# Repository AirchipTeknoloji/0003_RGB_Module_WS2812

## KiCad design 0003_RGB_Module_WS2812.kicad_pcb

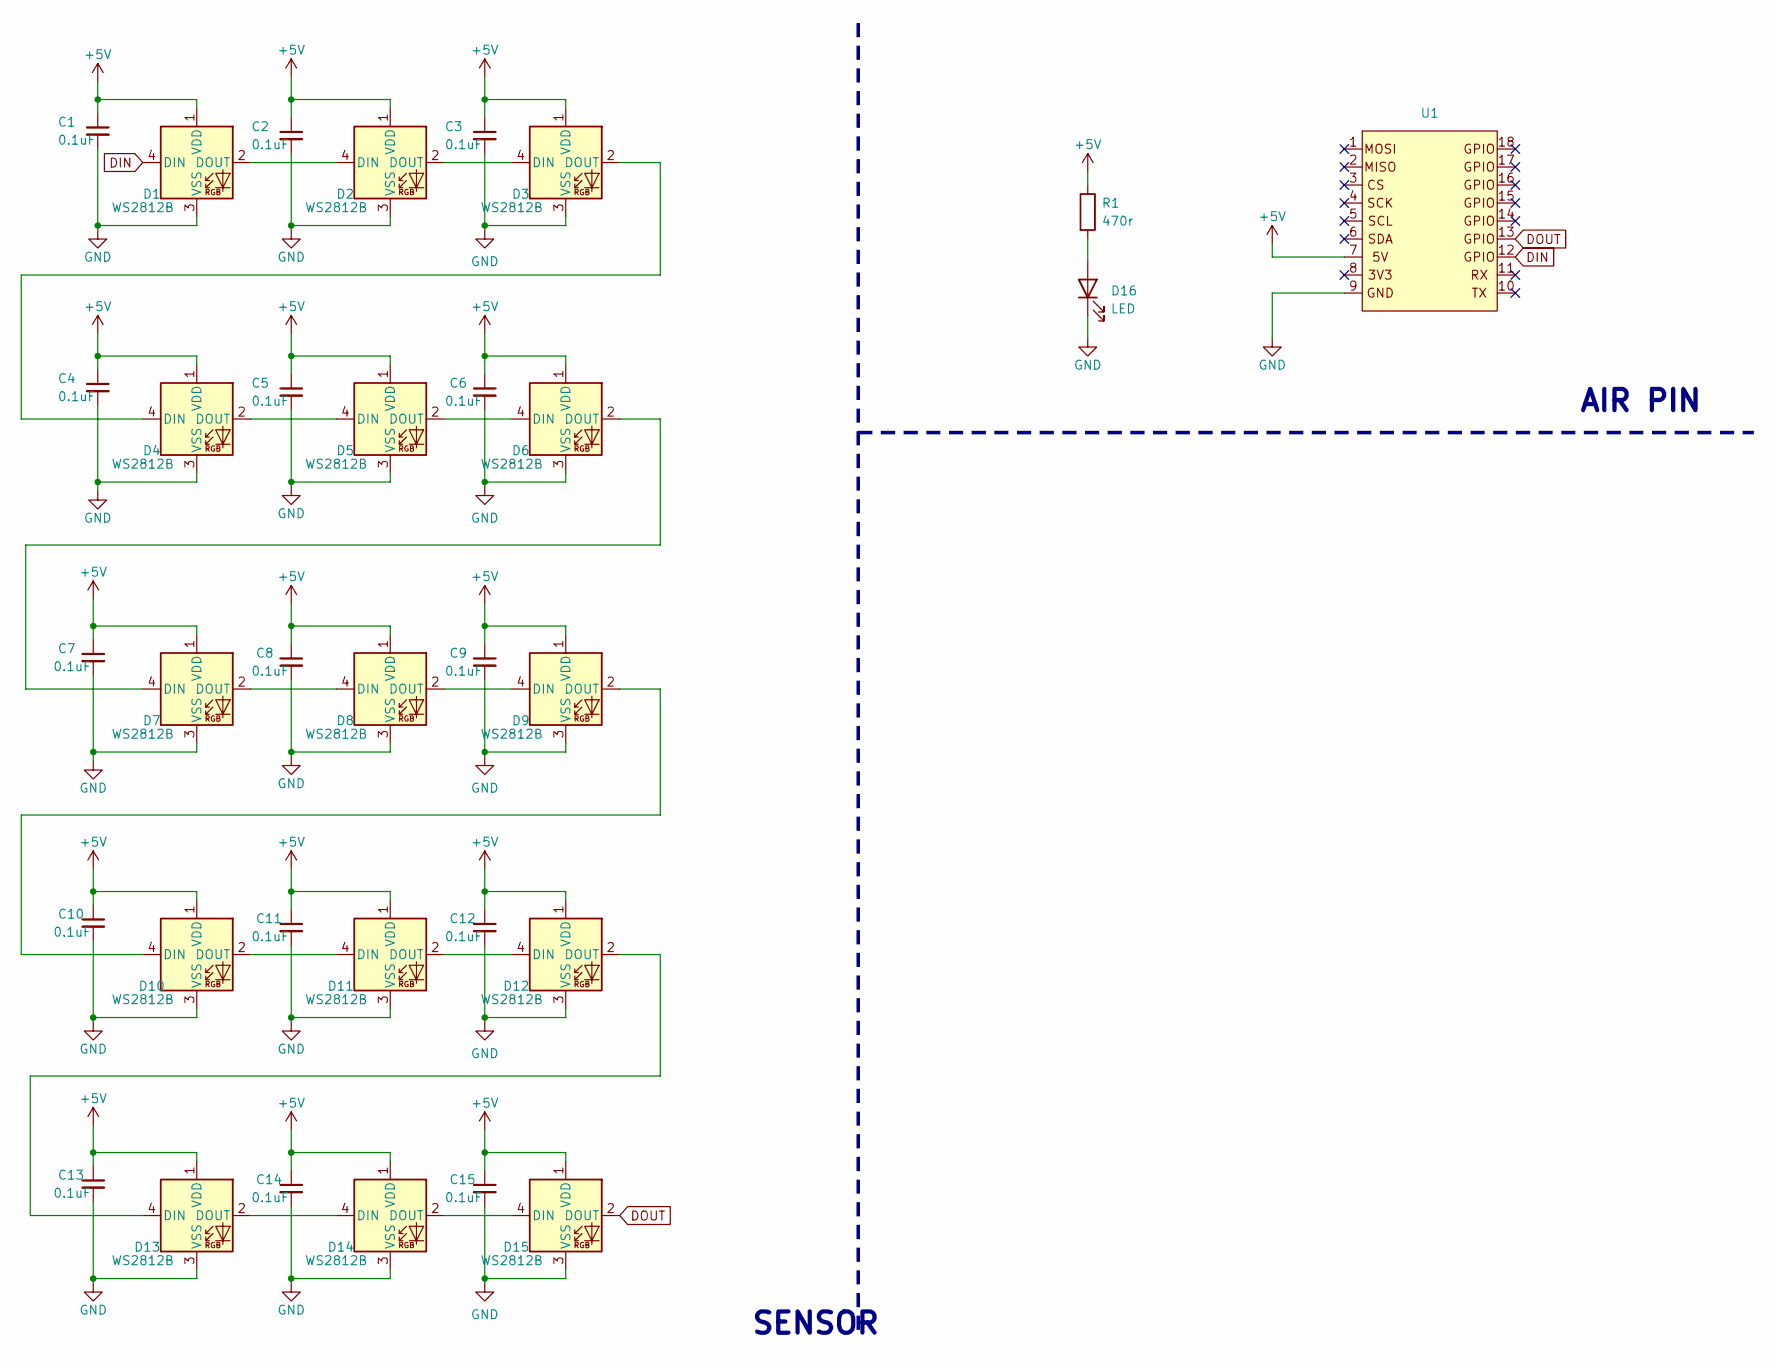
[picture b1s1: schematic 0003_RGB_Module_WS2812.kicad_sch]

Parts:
C1, C2, C3, C4, C5, C6, C7, C8, C9, C10, C11, C12, C13, C14, C15: 0.1uF; C_0603_1608Metric
D1, D2, D3, D4, D5, D6, D7, D8, D9, D10, D11, D12, D13, D14, D15: WS2812B; LED_WS2812B_PLCC4_5.0x5.0mm_P3.2mm
D16: LED; LED_0603_1608Metric
R1: 470r; R_0603_1608Metric
U1: pin_header_5-3

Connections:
+5V: C1.1, C2.1, C3.1, C4.1, C5.1, C6.1, C7.1, C8.1, C9.1, C10.1, C11.1, C12.1, C13.1, C14.1, C15.1, D1.1 (VDD), D2.1 (VDD), D3.1 (VDD), D4.1 (VDD), D5.1 (VDD), D6.1 (VDD), D7.1 (VDD), D8.1 (VDD), D9.1 (VDD), D10.1 (VDD), D11.1 (VDD), D12.1 (VDD), D13.1 (VDD), D14.1 (VDD), D15.1 (VDD), R1.1, U1.7
DIN: D1.4 (DIN), U1.12
DOUT: D15.2 (DOUT), U1.13
GND: C1.2, C2.2, C3.2, C4.2, C5.2, C6.2, C7.2, C8.2, C9.2, C10.2, C11.2, C12.2, C13.2, C14.2, C15.2, D1.3 (VSS), D2.3 (VSS), D3.3 (VSS), D4.3 (VSS), D5.3 (VSS), D6.3 (VSS), D7.3 (VSS), D8.3 (VSS), D9.3 (VSS), D10.3 (VSS), D11.3 (VSS), D12.3 (VSS), D13.3 (VSS), D14.3 (VSS), D15.3 (VSS), D16.1 (K), U1.9
unnamed: D1.2 (DOUT), D2.4 (DIN)
unnamed: D2.2 (DOUT), D3.4 (DIN)
unnamed: D3.2 (DOUT), D4.4 (DIN)
unnamed: D4.2 (DOUT), D5.4 (DIN)
unnamed: D5.2 (DOUT), D6.4 (DIN)
unnamed: D6.2 (DOUT), D7.4 (DIN)
unnamed: D7.2 (DOUT), D8.4 (DIN)
unnamed: D8.2 (DOUT), D9.4 (DIN)
unnamed: D9.2 (DOUT), D10.4 (DIN)
unnamed: D10.2 (DOUT), D11.4 (DIN)
unnamed: D11.2 (DOUT), D12.4 (DIN)
unnamed: D12.2 (DOUT), D13.4 (DIN)
unnamed: D13.2 (DOUT), D14.4 (DIN)
unnamed: D14.2 (DOUT), D15.4 (DIN)
unnamed: D16.2 (A), R1.2

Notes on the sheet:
AIR PIN
SENSOR

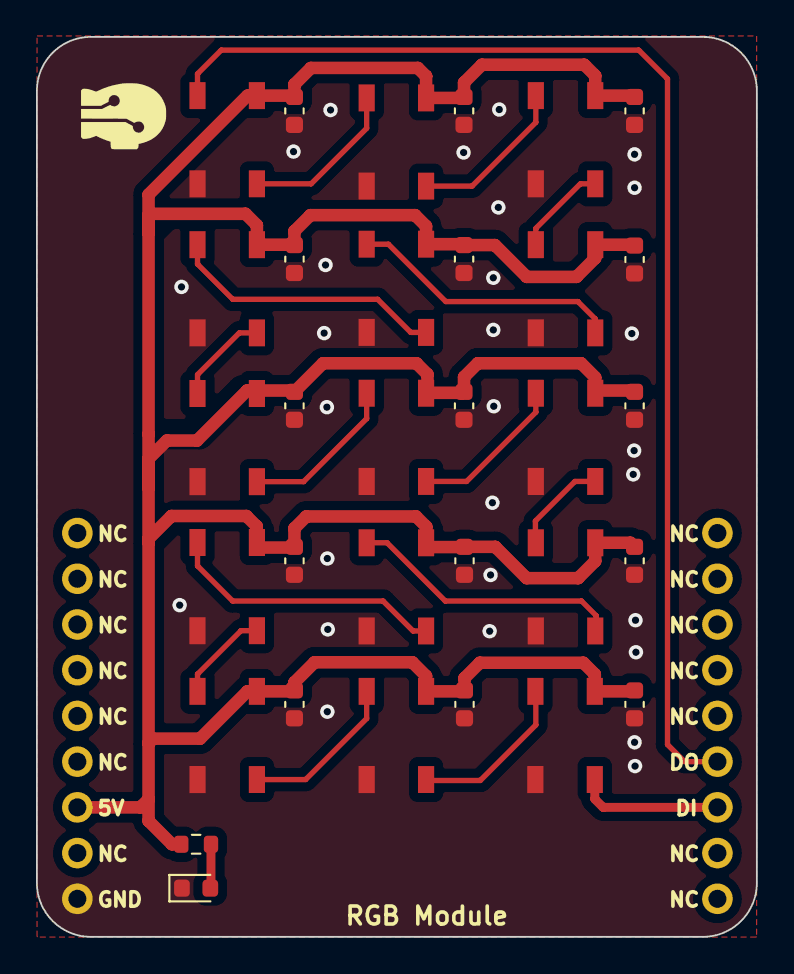
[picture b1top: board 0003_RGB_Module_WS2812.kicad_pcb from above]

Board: 2 copper layers, 40.0 x 50.0 mm, 33 parts (0 on the bottom side), 19 nets.
